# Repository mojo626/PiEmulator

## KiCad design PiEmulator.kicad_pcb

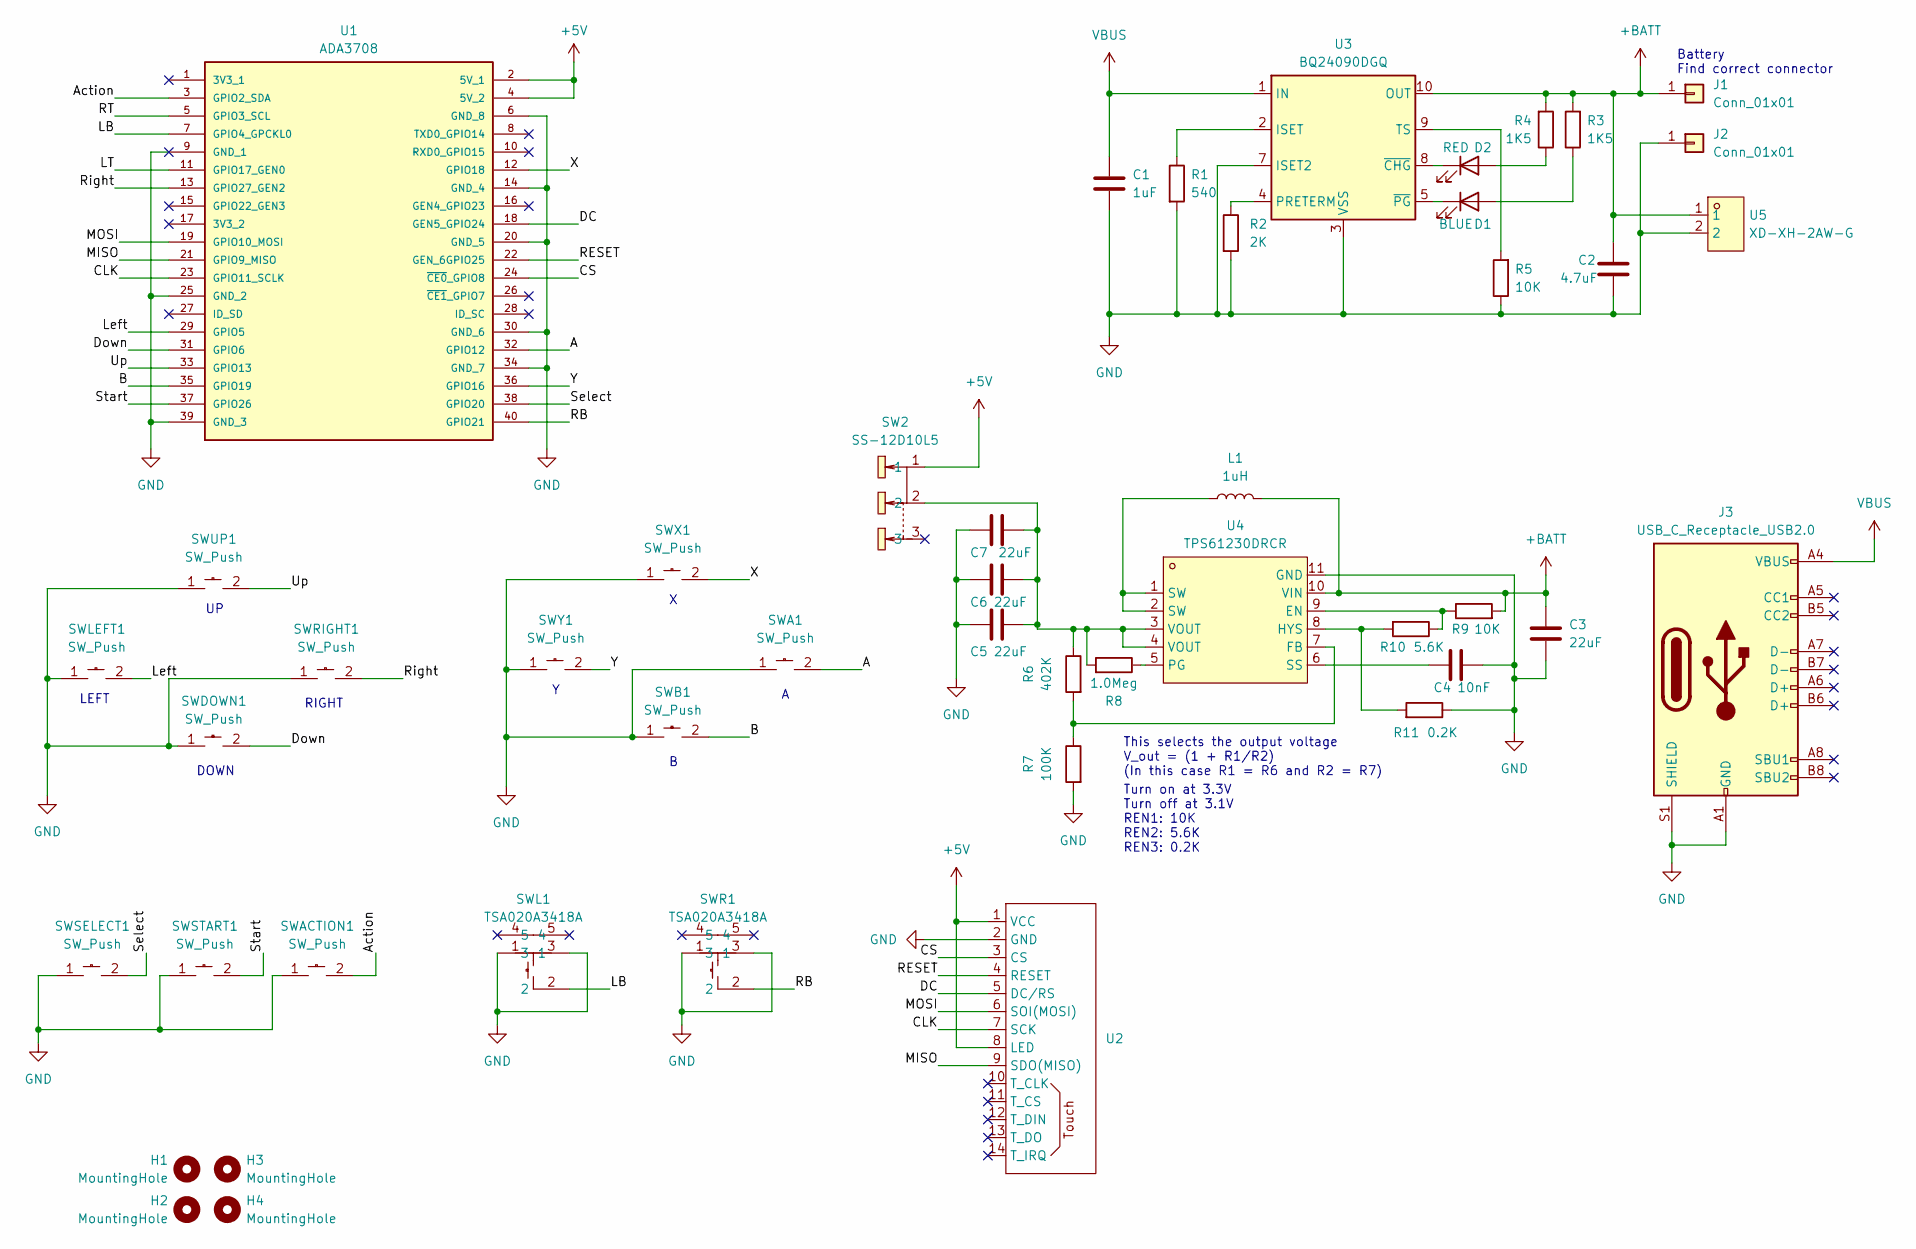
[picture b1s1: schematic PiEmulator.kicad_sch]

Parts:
C1: 1uF; C_0402_1005Metric
C2: 4.7uF; C_0603_1608Metric
C3, C5, C6, C7: 22uF; C_0805_2012Metric
C4: 10nF; C_0402_1005Metric
D1: BLUE; LED_0402_1005Metric
D2: RED; LED_0402_1005Metric
H1, H2, H3, H4: MountingHole; MountingHole_2.5mm
J1: Conn_01x01; SolderWirePad_4x4mm
J2: Conn_01x01; Solder_Pad_4x4mm
J3: USB_C_Receptacle_USB2.0; USB_C_Receptacle_HRO_TYPE-C-31-M-12
L1: 1uH; L_0603_1608Metric
R1: 540; R_0603_1608Metric
R2: 2K; R_0603_1608Metric
R3, R4: 1K5; R_0402_1005Metric
R5, R9: 10K; R_0402_1005Metric
R6: 402K; R_0603_1608Metric
R7: 100K; R_0603_1608Metric
R8: 1.0Meg; R_0603_1608Metric
R10: 5.6K; R_0603_1608Metric
R11: 0.2K; R_0603_1608Metric
SW2: SS-12D10L5; SW-TH_SS-12D10L5; LCSC Part C319012
SWA1: SW_Push; SW-SMD_4P-L6.2-W6.2-P4.00-LS7.0; LCSC Part C963191
SWACTION1: SW_Push; SW-SMD_4P-L6.2-W6.2-P4.00-LS7.0; LCSC Part C963191
SWB1: SW_Push; SW-SMD_4P-L6.2-W6.2-P4.00-LS7.0; LCSC Part C963191
SWDOWN1: SW_Push; SW-SMD_4P-L6.2-W6.2-P4.00-LS7.0; LCSC Part C963191
SWL1: TSA020A3418A; SW-SMD_TSA020XXXXXX; LCSC Part C2888437
SWLEFT1: SW_Push; SW-SMD_4P-L6.2-W6.2-P4.00-LS7.0; LCSC Part C963191
SWR1: TSA020A3418A; SW-SMD_TSA020XXXXXX; LCSC Part C2888437
SWRIGHT1: SW_Push; SW-SMD_4P-L6.2-W6.2-P4.00-LS7.0; LCSC Part C963191
SWSELECT1: SW_Push; SW-SMD_4P-L6.2-W6.2-P4.00-LS7.0; LCSC Part C963191
SWSTART1: SW_Push; SW-SMD_4P-L6.2-W6.2-P4.00-LS7.0; LCSC Part C963191
SWUP1: SW_Push; SW-SMD_4P-L6.2-W6.2-P4.00-LS7.0; LCSC Part C963191
SWX1: SW_Push; SW-SMD_4P-L6.2-W6.2-P4.00-LS7.0; LCSC Part C963191
SWY1: SW_Push; SW-SMD_4P-L6.2-W6.2-P4.00-LS7.0; LCSC Part C963191
U1: ADA3708; MODULE_ADA3708
U2: 4InchSPI
U3: BQ24090DGQ; HVSSOP-10-1EP_3x3mm_P0.5mm_EP1.57x1.88mm_ThermalVias
U4: TPS61230DRCR; VSON-10_L3.0-W3.0-P0.50-TL-EP_TPS61230DRCR; LCSC Part C139626
U5: XD-XH-2AW-G; CONN-TH_2P-P2.50_XH-2AW; LCSC Part C17700961

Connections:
+5V: SW2.1, U1.2 (5V_1), U1.4 (5V_2), U2.1 (VCC), U2.8 (LED)
+BATT: C2.1, C3.1, J1.1, L1.2, R3.2, R4.2, R9.2, U3.10 (OUT), U4.10 (VIN), U5.1
/A: SWA1.2, U1.32 (GPIO12)
/Action: SWACTION1.2, U1.3 (GPIO2_SDA)
/B: SWB1.2, U1.35 (GPIO19)
/CLK: U1.23 (GPIO11_SCLK), U2.7 (SCK)
/CS: U1.24 (~CE0_GPIO8), U2.3 (CS)
/DC: U1.18 (GEN5_GPIO24), U2.5 (DC/RS)
/Down: SWDOWN1.2, U1.31 (GPIO6)
/LB: SWL1.2, U1.7 (GPIO4_GPCKL0)
/LT: U1.11 (GPIO17_GEN0)
/Left: SWLEFT1.2, U1.29 (GPIO5)
/MISO: U1.21 (GPIO9_MISO), U2.9 (SDO(MISO))
/MOSI: U1.19 (GPIO10_MOSI), U2.6 (SOI(MOSI))
/RB: SWR1.2, U1.40 (GPIO21)
/RESET: U1.22 (GEN_6GPIO25), U2.4 (RESET)
/RT: U1.5 (GPIO3_SCL)
/Right: SWRIGHT1.2, U1.13 (GPIO27_GEN2)
/Select: SWSELECT1.2, U1.38 (GPIO20)
/Start: SWSTART1.2, U1.37 (GPIO26)
/Up: SWUP1.2, U1.33 (GPIO13)
/X: SWX1.2, U1.12 (GPIO18)
/Y: SWY1.2, U1.36 (GPIO16)
GND: C1.2, C2.2, C3.2, C4.2, C5.1, C6.1, C7.1, J2.1, J3.A1 (GND), J3.A12 (GND), J3.B1 (GND), J3.B12 (GND), J3.S1 (SHIELD), R1.2, R2.2, R5.1, R7.2, R11.1, SWA1.1, SWACTION1.1, SWB1.1, SWDOWN1.1, SWL1.1, SWL1.3, SWLEFT1.1, SWR1.1, SWR1.3, SWRIGHT1.1, SWSELECT1.1, SWSTART1.1, SWUP1.1, SWX1.1, SWY1.1, U1.6 (GND_8), U1.9 (GND_1), U1.14 (GND_4), U1.20 (GND_5), U1.25 (GND_2), U1.30 (GND_6), U1.34 (GND_7), U1.39 (GND_3), U2.2 (GND), U3.3 (VSS), U3.7 (ISET2), U3.11 (VSS), U4.11 (GND), U5.2
unnamed: C5.2, C6.2, C7.2, R6.1, R8.2, SW2.2, U4.3 (VOUT), U4.4 (VOUT)
unnamed: D1.2 (A), R3.1
unnamed: D1.1 (K), U3.5 (~PG)
unnamed: D2.2 (A), R4.1
unnamed: D2.1 (K), U3.8 (~CHG)
unnamed: L1.1, U4.1 (SW), U4.2 (SW)
unnamed: R1.1, U3.2 (ISET)
unnamed: R2.1, U3.4 (PRETERM)
unnamed: R5.2, U3.9 (TS)
unnamed: R9.1, R10.1, U4.9 (EN)
unnamed: R6.2, R7.1, U4.7 (FB)
unnamed: R10.2, R11.2, U4.8 (HYS)
unnamed: R8.1, U4.5 (PG)
unnamed: C4.1, U4.6 (SS)
VBUS: C1.1, J3.A4 (VBUS), J3.A9 (VBUS), J3.B4 (VBUS), J3.B9 (VBUS), U3.1 (IN)

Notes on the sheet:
DOWN
Turn on at 3.3V Turn off at 3.1V REN1: 10K REN2: 5.6K REN3: 0.2K
Battery Find correct connector
RIGHT
This selects the output voltage V_out = (1 + R1/R2) (In this case R1 = R6 and R2 = R7)
LEFT

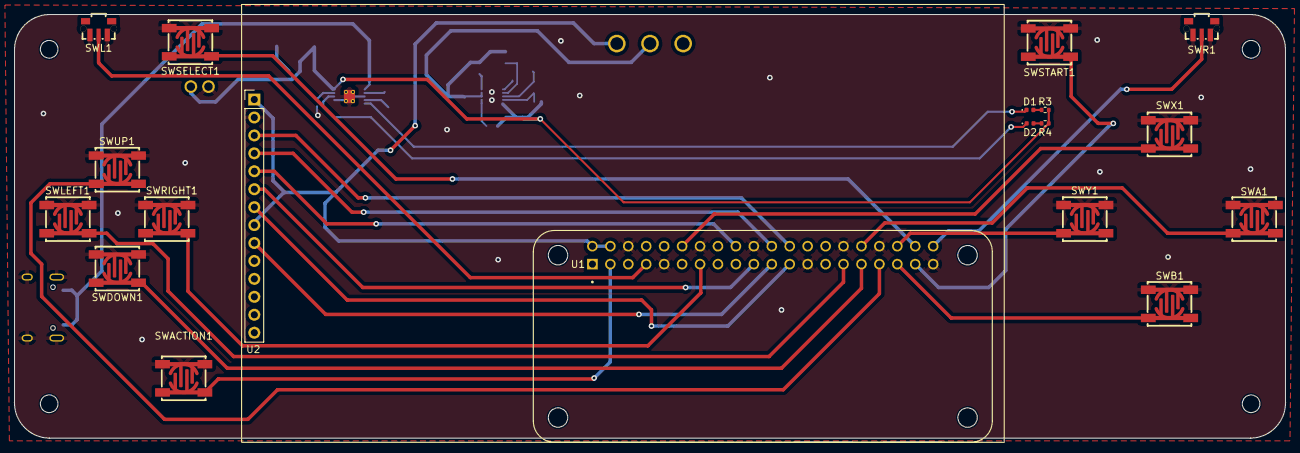
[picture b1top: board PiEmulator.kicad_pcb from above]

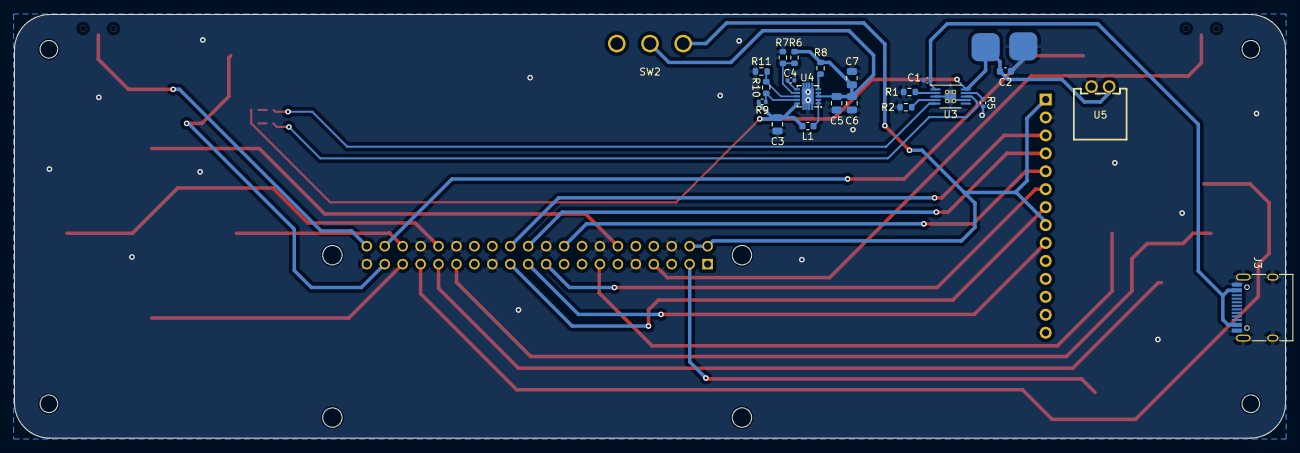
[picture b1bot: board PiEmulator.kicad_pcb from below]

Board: 2 copper layers, 180.0 x 60.0 mm, 47 parts (24 on the bottom side), 37 nets.

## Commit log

2024-03-10 first commit 2
2024-03-10 swapped buttons
2024-03-10 routed
2024-03-10 silkscreen + minor fixes
2024-03-12 added boost convertor
2024-03-12 bost routing + cleanup
2024-03-12 created step
2024-03-12 step changes
2024-03-12 added .wrl
2024-03-12 model changes
2024-03-13 added jst moved usb-c
2024-03-15 moved USBC, added battery connector
2024-03-15 moved usb-c
2024-03-18 added gerbers
2024-03-18 zip file
2024-03-18 manufacturing changes
